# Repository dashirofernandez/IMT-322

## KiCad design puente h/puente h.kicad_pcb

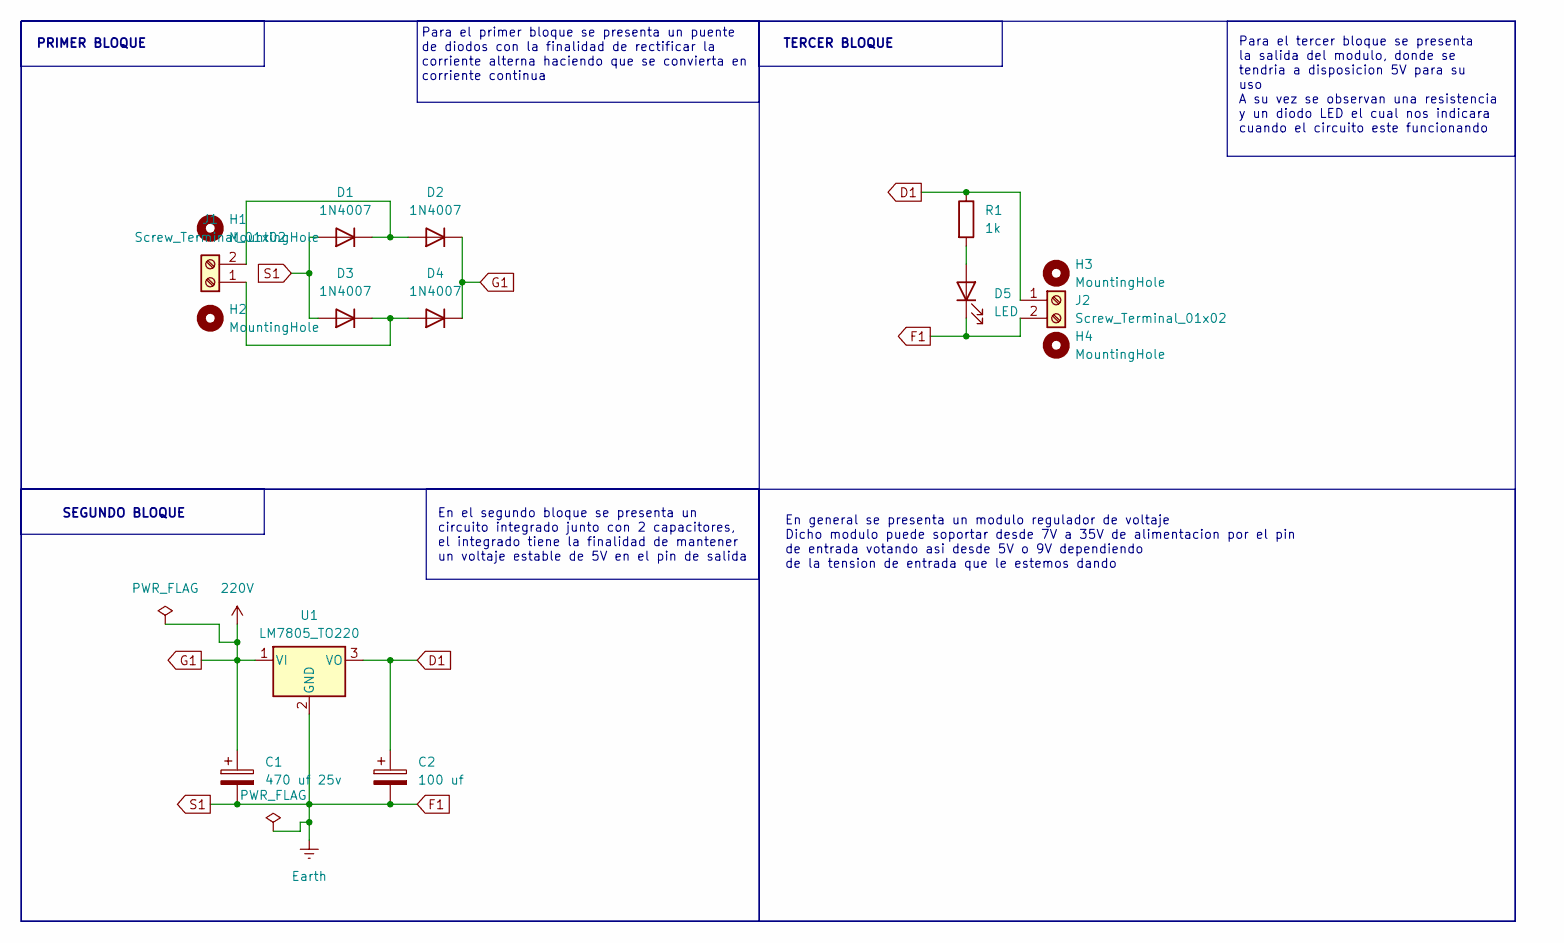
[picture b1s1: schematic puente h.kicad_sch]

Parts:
C1: 470 uf 25v; CP_Radial_D8.0mm_P3.50mm
C2: 100 uf; CP_Radial_D5.0mm_P2.50mm
D1, D2, D3, D4: 1N4007; D_DO-41_SOD81_P10.16mm_Horizontal
D5: LED; LED_D3.0mm
H1, H2, H3, H4: MountingHole; MountingHole_2.7mm_M2.5_Pad_TopOnly
J1, J2: Screw_Terminal_01x02; TerminalBlock_bornier-2_P5.08mm
R1: 1k; R_Axial_DIN0204_L3.6mm_D1.6mm_P7.62mm_Horizontal
U1: LM7805_TO220; TO-220-3_Vertical

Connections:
D1: C2.1, J2.1, R1.1, U1.3 (VO)
F1: C1.2, C2.2, D1.2 (A), D3.2 (A), D5.1 (K), J2.2, U1.2 (GND)
G1: C1.1, D2.1 (K), D4.1 (K), U1.1 (VI)
unnamed: D1.1 (K), D2.2 (A), J1.2
unnamed: D3.1 (K), D4.2 (A), J1.1
unnamed: D5.2 (A), R1.2

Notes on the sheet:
En el segundo bloque se presenta un circuito integrado junto con 2 capacitores, el integrado tiene la finalidad de mantener un voltaje estable de 5V en el pin de salida
TERCER BLOQUE
Para el primer bloque se presenta un puente de diodos con la finalidad de rectificar la corriente alterna haciendo que se convierta en corriente continua
PRIMER BLOQUE
En general se presenta un modulo regulador de voltaje Dicho modulo puede soportar desde 7V a 35V de alimentacion por el pin de entrada votando asi desde 5V o 9V dependiendo de la tension de entrada que le estemos dando
Para el tercer bloque se presenta la salida del modulo, donde se tendria a disposicion 5V para su uso A su vez se observan una resistencia y un diodo LED el cual nos indicara cuando el circuito este funcionando
SEGUNDO BLOQUE

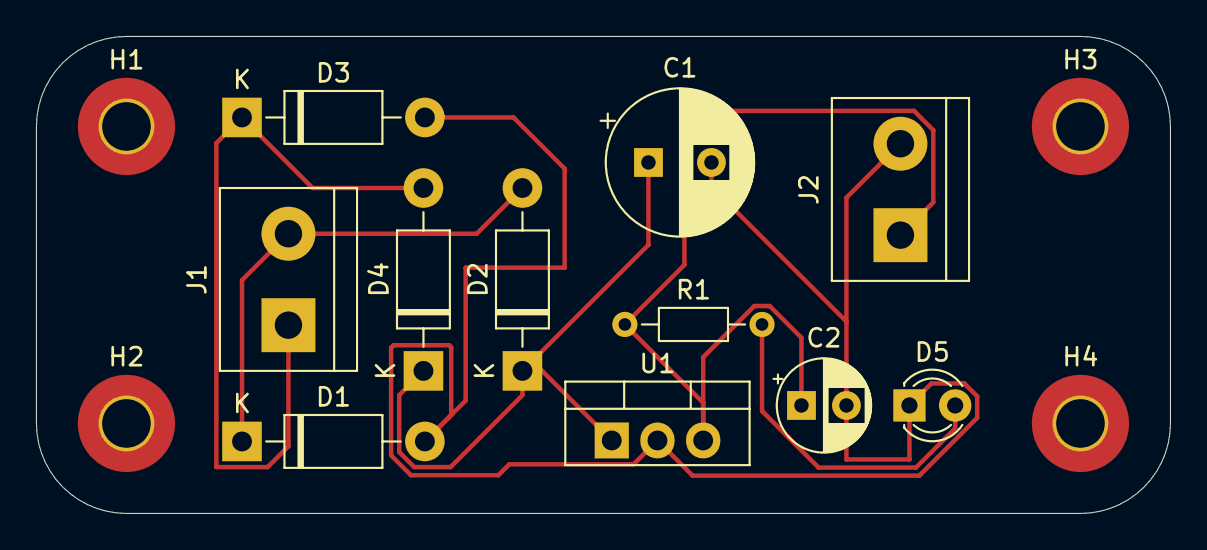
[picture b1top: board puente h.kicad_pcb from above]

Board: 2 copper layers, 63.0 x 26.5 mm, 15 parts (0 on the bottom side), 6 nets.

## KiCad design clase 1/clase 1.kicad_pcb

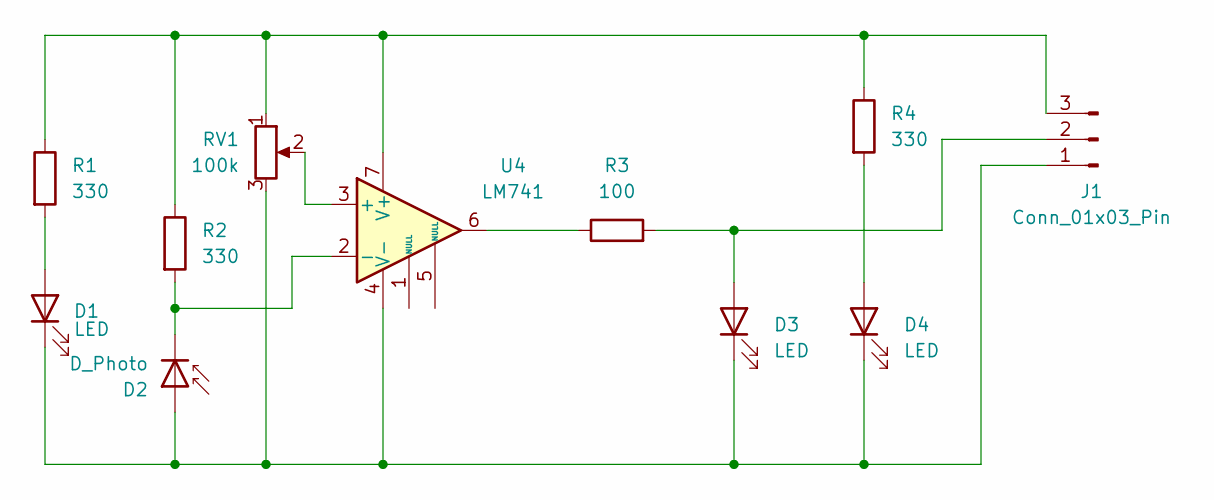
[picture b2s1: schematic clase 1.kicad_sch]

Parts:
D1: LED; LED_D4.0mm
D2: D_Photo; LED_D4.0mm
D3, D4: LED; LED_0805_2012Metric_Pad1.15x1.40mm_HandSolder
J1: Conn_01x03_Pin; PinHeader_1x03_P2.54mm_Horizontal
R1, R2, R4: 330; R_0805_2012Metric
R3: 100; R_0805_2012Metric
RV1: 100k; Potentiometer_ACP_CA9-V10_Vertical_Hole
U4: LM741; TSSOP-8_3x3mm_P0.65mm

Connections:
unnamed: D1.2 (A), R1.2
unnamed: D1.1 (K), D2.2 (A), D3.1 (K), D4.1 (K), J1.1, RV1.3, U4.4 (V-)
unnamed: D2.1 (K), R2.2, U4.2 (-)
unnamed: D3.2 (A), J1.2, R3.2
unnamed: D4.2 (A), R4.2
unnamed: J1.3, R1.1, R2.1, R4.1, RV1.1, U4.7 (V+)
unnamed: R3.1, U4.6
unnamed: RV1.2, U4.3 (+)

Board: 2 copper layers, 11 parts (0 on the bottom side), 8 nets, no tracks yet.

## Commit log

2024-02-17 nombre
2024-02-17 codigo arduino esp32
2024-02-24 ejercicio 1 embebidos
2024-02-24 ejercicio1punto2
2024-03-02 ejercicio 2 punto 2
2024-03-09 ejercicio3punto1
2024-04-13 sensor infrarojo
2024-04-20 semaforo
2024-04-21 ultrasonico
2024-04-22 placa reductora de voltaje
2024-04-23 practica ascensor
2024-04-25 ascensor
2024-04-25 ascensor#
2024-04-27 examen practico nro 2
2024-05-22 blink rapsberry pi 3
2024-05-28 prueba rasp
